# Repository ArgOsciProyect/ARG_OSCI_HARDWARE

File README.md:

# ARG_OSCI Hardware Implementation Guide

**ARG_OSCI** is an open-source portable oscilloscope platform. This document details the technical implementation of the hardware, focusing on design decisions, construction, and improvement opportunities. It is intended for engineers and advanced users interested in building or modifying the device.

---

## Table of Contents
- [Introduction](#introduction)
- [Design Overview](#design-overview)
- [Implementation Details](#implementation-details)
  - [1. Input Network](#1-input-network)
  - [2. Attenuation Networks](#2-attenuation-networks)
    - [2.1 A/B Attenuation Network](#ab-attenuation-network)
    - [2.2 1/2/3/4 Attenuation Network](#1234-attenuation-network)
    - [2.3 Attenuation Stage Details](#attenuation-stage-details)
  - [3. Amplification Stage](#3-amplification-stage)
  - [4. Signal Filtering](#4-signal-filtering)
  - [5. External ADC Circuit](#5-external-adc-circuit)
  - [6. Transient Comparator Circuit](#6-transient-comparator-circuit)
  - [7. Calibration Square Wave Generator](#7-calibration-square-wave-generator)
  - [8. Connection Status LED Circuit](#8-connection-status-led-circuit)
  - [9. Power Supply](#9-power-supply)
  - [10. ESP32 Connectivity and Decoupling](#10-esp32-connectivity-and-decoupling)
- [Design Files and Resources](#design-files-and-resources)
- [Construction and Improvement Notes](#construction-and-improvement-notes)
  - [1. Assembly and Component Selection](#assembly-and-component-selection)
  - [2. Protection and Safety](#protection-and-safety)
  - [3. Optional Simplifications](#optional-simplifications)
  - [4. Design and Layout](#design-and-layout)
  - [5. PCB Design](#pcb-design)
  - [6. 3D Case Design](#3d-case-design)
- [Pending Tasks and Recommendations](#pending-tasks-and-recommendations)
  - [1. Technical Improvements](#technical-improvements)
  - [2. Documentation and Usability](#documentation-and-usability)
  - [3. Future Development](#future-development)
- [License](#license)
- [Acknowledgements](#acknowledgements)

---

## Introduction

This document describes how to implement the ARG_OSCI hardware, including the rationale behind each design block, construction notes, and suggestions for further development. For usage instructions, refer to the user manual.

## Design Overview

The hardware is divided into several functional blocks:

- Input Network
- Attenuation Networks
- Attenuation Stage Details
- Amplification Stage
- Signal Filtering
- External ADC Circuit
- Transient Comparator Circuit
- Calibration Square Wave Generator
- Connection Status LED Circuit
- Power Supply
- ESP32 Connectivity and Decoupling

---

## Implementation Details

### 1. Input Network

The input network provides both AC and DC coupling paths. The AC coupling path includes a series capacitor (150 nF), while the DC path is direct. The 150 nF capacitor must be rated for at least 500V to safely block DC voltages up to the device's maximum scale (±400V). The capacitor value was selected to achieve a cutoff frequency below 1 Hz, considering that the input impedance is always greater than 1MΩ (typically 1070 MΩ to 1500 MΩ, depending on the attenuation setting). This configuration forms a high-pass filter and ensures accurate measurement of AC signals above 1Hz, with a settling time of approximately 1 second after switching to AC coupling.

<!--**Expansion note:** You may add a graph of the high-pass filter response.-->

### 2. Attenuation Networks
#### 2.1. A/B Attenuation Network
Provides coarse attenuation (e.g., ×40) using resistor dividers and mechanical switches (2P2T selector switch).

#### 2.2. 1/2/3/4 Attenuation Network
Provides fine attenuation (e.g., ×2.4), yielding eight selectable voltage ranges in combination with the A/B network. This stage also uses mechanical switches (2P4T selector switch) and resistor divider networks for attenuation.

#### 2.3. Attenuation Stage Details

The decision to use resistive divider networks in the attenuation stage was made after a thorough analysis of various possible configurations. Different approaches were evaluated based on criteria such as ease of compensation, the number of switches required for implementation, the impedance presented to the amplifier, and other relevant aspects. The chosen solution represents a balance between precision, simplicity, and robustness for the application.

The attenuation stage is designed to maintain an input impedance greater than 1 MΩ. To compensate for the effects of parasitic capacitances —particularly those introduced by the amplifier— capacitors are included in the attenuation network. The total input capacitance of the device is kept below 20pF. Components are selected with 5% tolerance (1% for higher precision if desired), resistors are rated at 1/4 W, and capacitors are rated for at least 25 V, except for the series capacitor in stage B, which must withstand up to 500 V to safely attenuate signals up to 400V when required.

A trimmer capacitor is placed at the amplifier input to allow fine adjustment and compensate for variations in the amplifier’s input capacitance and other component tolerances. The trimmer is adjustable up to 20pF, with a minimum value of approximately 4.2pF, ensuring a flat frequency response across the device’s bandwidth. The most sensitive stage to these variations is A2, as it has the smallest capacitance in parallel with the amplifier, making it more susceptible to frequency response deviations.

### 3. Amplification Stage

The amplification stage uses the TL082 operational amplifier, chosen for its suitable bandwidth, slew rate, operating ranges, low associated errors, low cost, and ease of sourcing. Two feedback configurations are implemented: the inverting configuration is used to set the signal offset (centering it within the ADC input range using the –5V rail), while the non-inverting configuration amplifies the measured signal to maximize the ADCs' dynamic range.

To minimize errors due to input bias currents, high-value resistors are used in the feedback network. This necessitated the inclusion of a capacitive compensation network (without the need for a trimmer in this case).

<!--**Expansion note:** Discuss op-amp selection criteria, possible improvements, and test results.-->

#### Design Considerations and Potential Improvements
- **Resistor Value Optimization:** It is being considered to reduce the values of the feedback resistors, as the error from bias currents is relatively low. Lowering these values could allow the removal of the compensation network, though a capacitor should still be retained to filter noise from the –5V supply. This change would increase the device's power consumption and should be evaluated accordingly.
- **Negative Voltage Limiter:** It is recommended to add a negative voltage limiter at the amplifier output. While the amplifier typically saturates at positive voltages (not damaging the ADCs), under certain conditions it may output voltages below 0V, which could potentially harm the ADCs.

### 4. Signal Filtering

A conventional first-order RC low-pass filter is used for signal filtering. The filters are designed based on the input capacitance of the ADCs used in each case. Two separate filter networks are implemented, allowing the user to select which ADC to use. For each network, the cutoff frequency is set to the maximum frequency that the device can accurately measure with the selected ADC.

#### Design Considerations and Potential Improvements
- **Filter Effectiveness Review:** It has been observed that at higher frequencies, aliasing phenomena may occur, distorting the measured signal and its frequency spectrum. A review of the filter effectiveness is recommended, and higher-order filters may be considered to improve performance and reduce aliasing effects.

### 5. External ADC Circuit

The external ADC (ADS7884) circuit is designed following the manufacturer's recommendations. For SPI communication with the ESP32, the layout ensures physical proximity between the ADS7884 and the relevant ESP32 pins, with all SPI traces kept as short and equal in length as possible. These measures are critical to maintain signal integrity at the 40 MHz communication frequency.

The ADS7884 is powered by the 3.3 V supply provided by the ESP32's onboard regulator, which also serves as the ADC's voltage reference. The stability of this voltage is crucial for measurement accuracy. To stabilize the supply, an RC network is implemented, consisting of the manufacturer-recommended capacitors and a 100 Ω resistor (subject to further review), in line with the recommended power supply impedance.

#### Design Considerations and Potential Improvements
- **Dedicated Voltage Regulator:** It is recommended to consider adding a dedicated voltage regulator for the ADC to ensure a stable reference voltage, independent of noise from the ESP32 supply.
- **Power Supply Filtering Review:** The value of the series resistor and the overall RC network should be reviewed and optimized to further improve voltage stability and measurement quality.
- **EMI/Environmental Noise Shielding:** The ADC has shown sensitivity to environmental interference and noise. It is recommended to implement shielding methods on the PCB or enclosure to reduce these effects and improve measurement reliability.

### 6. Transient Comparator Circuit

The transient comparator circuit enables the detection and reading of aperiodic (transient) signals. It consists of three main parts, each with a specific function:

#### RC Filter
The RC filter stabilizes a PWM signal generated by the ESP32. This PWM signal is set to have an average voltage equal to the trigger level selected in the application for signal visualization. The resulting DC voltage serves as the reference level for the comparator.

#### Comparator (TL082)
The remaining amplifier in the TL082 IC is configured as a comparator. It compares the measured signal to the reference voltage from the RC filter. When the input signal exceeds the trigger threshold, the comparator switches its output state. This transition is recognized as a transient event, which is then communicated to the application for display.

#### Digital Signal Adapter
The digital adapter converts the output of the comparator to voltage levels that are safe and readable by the ESP32: 3.3 V (minimum 2.475 V) for logic high and 0 V (maximum 0.825 V) for logic low. This is achieved using a BAT54 (or BAT85) diode in combination with a resistive divider, which limits current and ensures the output is pulled close to 0 V when the comparator switches to its negative output.

<!--**Expansion note:** Add timing diagrams or oscilloscope captures of transient detection events.-->

### 7. Calibration Square Wave Generator

The calibration circuit operates using a 1 kHz square wave signal provided by the ESP32, with levels ranging from 0 V to 3.3 V. This signal is attenuated to approximately 30% of its original amplitude using a resistive divider (15 kΩ and 6.8 kΩ), resulting in a safe level for the A2 stage, which is particularly sensitive to parasitic capacitance. The attenuated signal is used specifically to fine-tune the trimmer capacitor in the A2 stage. The resistor values are selected to minimize current draw and reduce loading on the ESP32 output.

### 8. Connection Status LED Circuit

The purpose of this LED is to indicate when the ESP32 board is ready to accept WiFi connections and begin operation. While the LED is off, the device is generating the access point. When the LED turns on, it signals that the user can connect to the device.

A 5 mm LED is used to increase visibility. A 270 Ω resistor is placed in series, but this value can be adjusted if needed—for example, using a lower resistance to increase brightness. The LED size and resistor value can be modified according to specific design preferences.

### 9. Power Supply
#### 9.1. +5V Supply
- The +5V supply is sourced from the ESP32's 5V pin, which itself is powered via the USB port.
- A diode-capacitor circuit is used between the USB input and the 5V rail. The presence of the diode causes a slight voltage drop below 5V. While this does not affect the operation of the operational amplifiers, it does slightly shift the voltage levels in the comparator circuit and significantly impacts the generation of the –5V rail via the LM2776.

#### 9.2. –5V Supply
- The –5V rail is generated using the LM2776 charge pump IC, implemented according to the manufacturer's recommendations.
- Stabilization and voltage generation capacitors are placed as close as possible to the LM2776 to ensure proper operation and minimize noise.
- Since the LM2776 inverts and slightly alters the positive supply voltage, software and firmware corrections are applied to compensate for any offset shifts that could affect ADC readings.
- There is a known issue with the LM2776 operation that requires further review to ensure reliable negative voltage generation.

#### 9.3. External Power Option
- The PCB provides access to power supply pins, allowing the circuit to be powered externally. This enables bypassing the micro USB and ESP32 for power delivery, and allows for a higher-quality negative voltage supply if needed.

### 10. ESP32 Connectivity and Decoupling
#### 10.1. Future Improvements
- **Direct Microcontroller Integration:** There are plans to redesign the hardware to use only the ESP32 microcontroller chip, eliminating the full devkit. This would:
  - Reduce the overall PCB size
  - Simplify flashing and programming
  - Improve signal routing and reduce parasitic effects
  - Allow for more flexible and compact enclosure designs
  - Potentially reduce cost and improve reliability

---

## Design Files and Resources
- **Schematics**: Complete circuit diagrams for all hardware blocks. Located in the ['Schematics'](Schematics/) folder.
- **PCB Layout**: Proposed PCB design with Gerber files for manufacturing. Located in the ['PCB'](PCB/) folder.
- **BOM**: Bill of Materials with recommended part numbers and tolerances. Available in the ['BOM'](BOM/) folder.
- **3D Enclosure**: Printable STL files for the device enclosure. Available in the ['Case3D'](Case3D/) folder.
- **LTspice Simulations**: Circuit simulation files for analysis and design validation. Recommended folder name: ['LTspice_Simulations'](LTspice_Simulations/).

> **Additional files:**
- Technical documentation and manuals in the ['Doc'](Doc/) folder.
- Images and diagrams in the ['Images'](Images/) folder.

---

## Construction and Improvement Notes

### 1. Assembly and Component Selection
- For best measurement accuracy, use 1% tolerance components in the following order of priority:
  1. Amplification circuit (affects all scales and frequencies)
  2. A/B attenuation circuit (affects upper half of scales, 40x attenuation)
  3. Series capacitor in the 1/2/3/4 attenuation circuit (affects all scales at high frequency)
  4. 1/2/3/4 attenuation circuit (affects all scales)
  5. Input filters to the ADCs
  6. Remaining components
- Both the internal ESP32 ADC and the external ADC present nonlinearities, though the external ADC is more accurate.
- Pay special attention to the correct wiring of the attenuation scales and selector logic during assembly. Errors here can damage multiple components.

### 2. Protection and Safety
- It is strongly recommended to add fuse-varistor protection circuits to safeguard the integrity of the attenuation stages:
  - 12.5 V varistor in stage A
  - 500 V varistor in stage B
  - 5 V varistor in stage 1 (direct path to the op-amp)

Note: The current PCB does not include footprints for these components.

### 3. Optional Simplifications
- The following stages can be omitted to reduce PCB size, simplify construction, or save on materials:
  - B attenuation stage (if high-voltage operation is not required)
  - AC/DC selection stage
  - Single-shot mode stage
  - ADC input filter for any unused ADC
- If the LM2776 IC is unavailable, substitute with a similar IC (ensure correct pinout) or provide a negative voltage rail externally.

### 4. Design and Layout
- PCB layout can be further optimized for EMC and signal integrity.
- The enclosure design may be adapted or improved for robustness.
- More compact PCB designs are planned, including protection features and direct microcontroller integration (without the devkit).

### 5. PCB Design
The PCB was designed following standard practices, prioritizing functional block separation and signal integrity as described in previous sections. No special layout considerations beyond those already mentioned were required.

### 6. 3D Case Design
The 3D case was designed to fit the PCB and provide basic protection. No special design constraints or requirements were considered beyond ensuring proper fit.

> **Note:** If electromagnetic shielding is desired to reduce interference, keep in mind that the device connects via WiFi. Any shielding solution should be implemented with care to avoid degrading wireless communication performance.

---

## Pending Tasks and Recommendations

### 1. Technical Improvements
- Complete a detailed error analysis and document the results for all acquisition paths.
- Review and improve the negative power supply design, including alternatives to the LM2776.
- Consider implementing higher-order input filters to improve signal fidelity and reduce aliasing.
- Evaluate and document the effectiveness of protection circuits and their impact on measurement reliability.

### 2. Documentation and Usability
- Provide step-by-step assembly instructions and detailed test procedures.
- Add troubleshooting and known issues sections to assist users during assembly and operation.

### 3. Future Development
- Develop and release more compact PCB designs with integrated protections and without the devkit.
- Explore the possibility of omitting or modularizing optional stages for different use cases.

---

## License

This hardware project is licensed under the [CERN-OHL-W v2](https://gitlab.com/ohwr/project/cernohl/-/wikis/home).

---

## Acknowledgements

This project is part of the **ARG_OSCI** oscilloscope visualization tool suite. For firmware and software, visit the [ARG_OSCI_FIRMWARE](https://github.com/ArgOsciProyect/ARG_OSCI_FIRMWARE) and [ARG_OSCI_APP](https://github.com/ArgOsciProyect/ARG_OSCI_APP) repositories.

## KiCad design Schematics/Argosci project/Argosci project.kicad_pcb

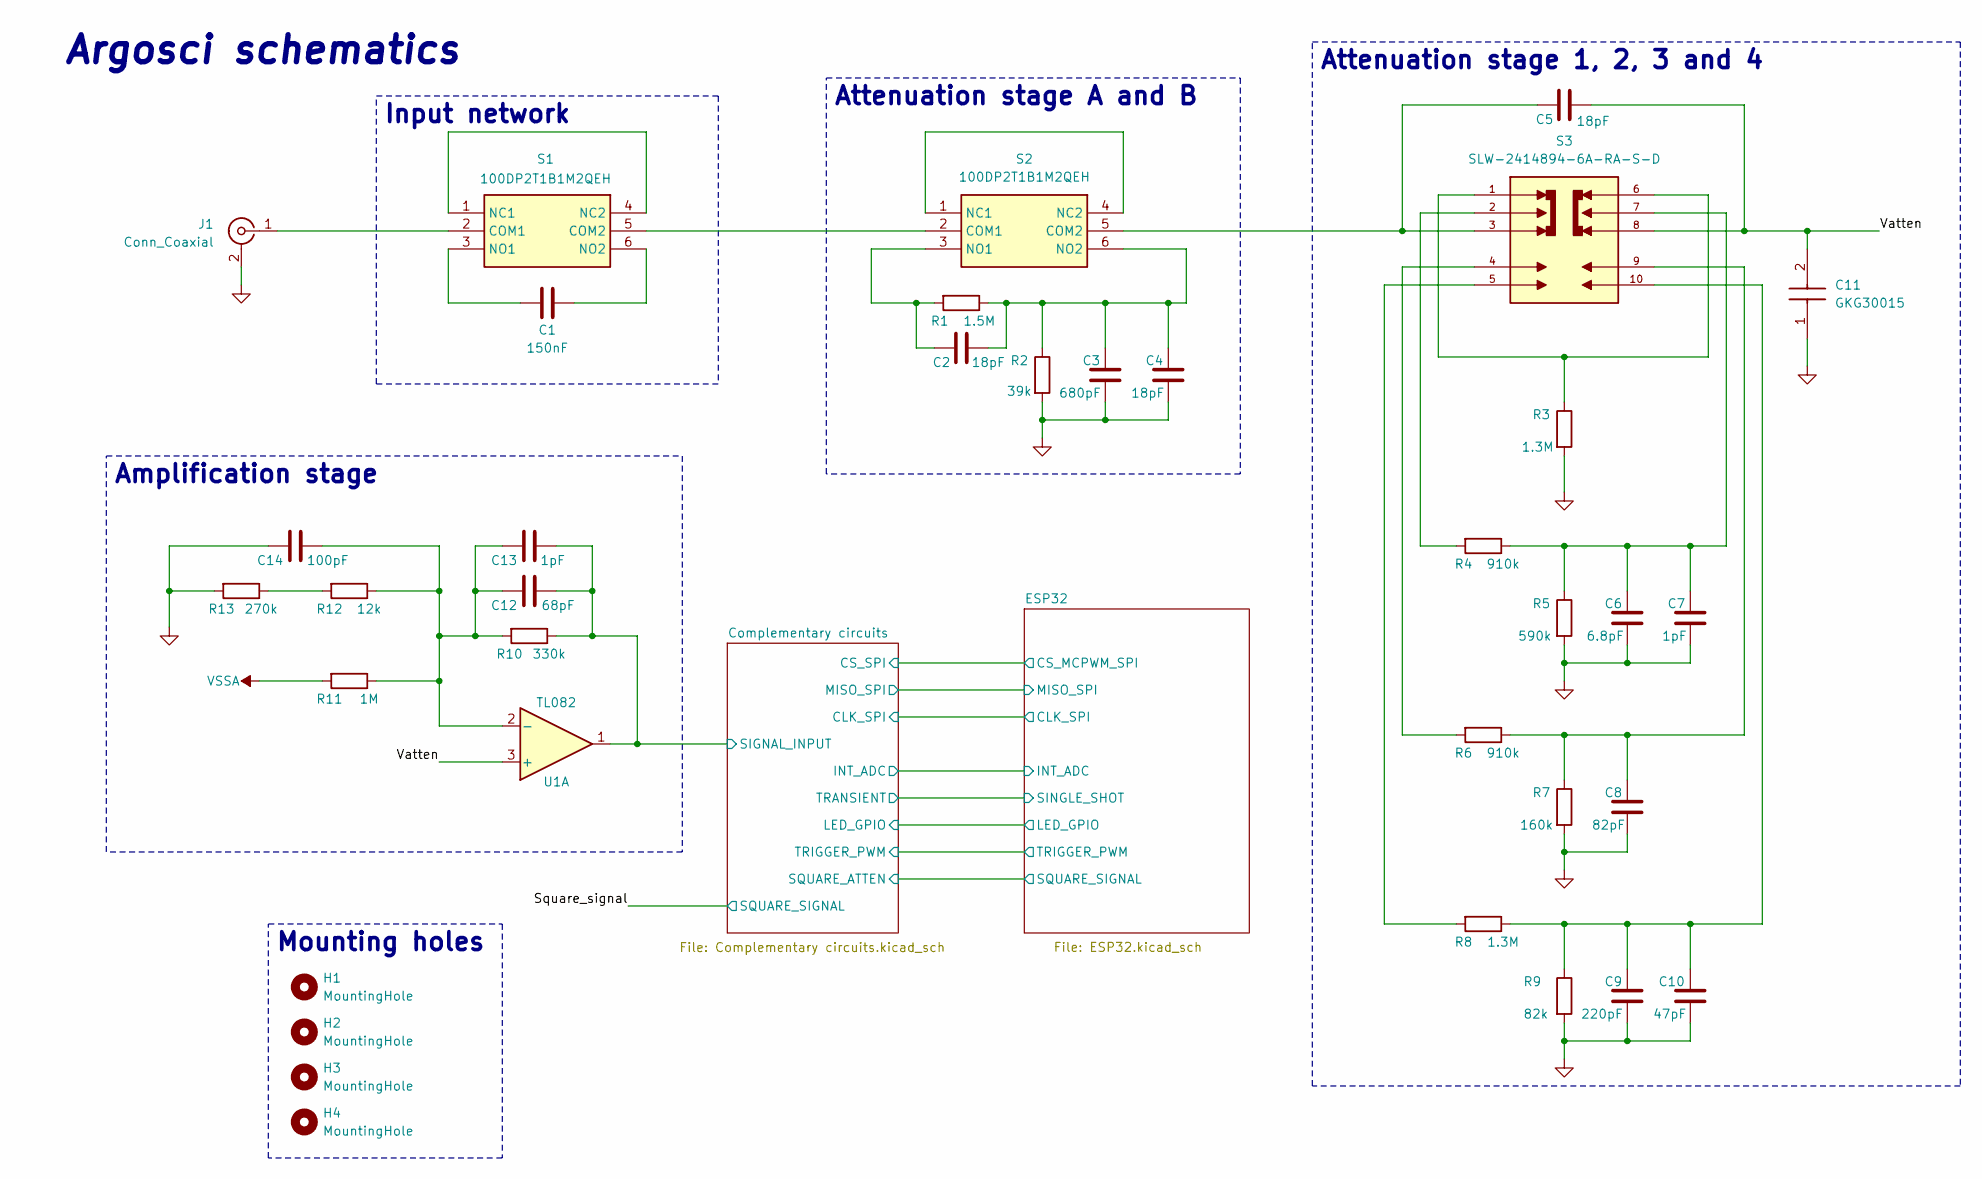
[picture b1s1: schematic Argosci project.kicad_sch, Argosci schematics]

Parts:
C1: 150nF; C_1206_3216Metric
C2, C4, C5: 18pF; C_1206_3216Metric
C3: 680pF; C_1206_3216Metric
C6: 6.8pF; C_1206_3216Metric
C7, C13: 1pF; C_1206_3216Metric
C8: 82pF; C_1206_3216Metric
C9: 220pF; C_1206_3216Metric
C10: 47pF; C_1206_3216Metric
C11: GKG30015; Mouser Part Number 659-GKG30015
C12: 68pF; C_1206_3216Metric
C14: 100pF; C_1206_3216Metric
H1, H2, H3, H4: MountingHole; MountingHole_3mm
J1: Conn_Coaxial; BNC_Amphenol_B6252HB-NPP3G-50_Horizontal
R1: 1.5M; R_1206_3216Metric
R2: 39k; R_1206_3216Metric
R3, R8: 1.3M; R_1206_3216Metric
R4, R6: 910k; R_1206_3216Metric
R5: 590k; R_1206_3216Metric
R7: 160k; R_1206_3216Metric
R9: 82k; R_1206_3216Metric
R10: 330k; R_1206_3216Metric
R11: 1M; R_1206_3216Metric
R12: 12k; R_1206_3216Metric
R13: 270k; R_1206_3216Metric
S1, S2: 100DP2T1B1M2QEH; Mouser Part Number 612-100DP2T1B1M2QEH
S3: SLW-2414894-6A-RA-S-D; SW_SLW-2414894-6A-RA-S-D; PARTREV 1.01
U1: TL082; DIP-8_W7.62mm

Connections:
/Complementary circuits/SIGNAL_INPUT: C12.2, C13.2, R10.1, U1.1; also elsewhere on the board
/Vatten: C5.2, C11.2, S3.8, U1.3 (+)
GND: C3.2, C4.2, C6.2, C7.2, C8.2, C9.2, C10.2, C11.1, C14.1, J1.2 (Ext), R2.2, R3.2, R5.2, R7.2, R9.2, R13.2; also elsewhere on the board
unnamed: C6.1, C7.1, R4.1, R5.1, S3.7
unnamed: C8.1, R6.1, R7.1, S3.9
unnamed: C9.1, C10.1, R8.1, R9.1, S3.10
unnamed: J1.1 (In), S1.2 (COM1)
unnamed: R3.1, S3.1, S3.6
unnamed: R4.2, S3.2
unnamed: R6.2, S3.4
unnamed: R8.2, S3.5
unnamed: R12.2, R13.1
unnamed: S1.5 (COM2), S2.2 (COM1)
unnamed: S1.1 (NC1), S1.4 (NC2)
unnamed: C1.1, S1.3 (NO1)
unnamed: C1.2, S1.6 (NO2)
unnamed: C5.1, S2.5 (COM2), S3.3
unnamed: S2.1 (NC1), S2.4 (NC2)
unnamed: C2.1, R1.2, S2.3 (NO1)
unnamed: C2.2, C3.1, C4.1, R1.1, R2.1, S2.6 (NO2)
unnamed: C12.1, C13.1, C14.2, R10.2, R11.1, R12.1, U1.2 (-)
VSSA: R11.2; also elsewhere on the board

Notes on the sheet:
Argosci schematics
Input network
Mounting holes
Amplification stage
Attenuation stage 1, 2, 3 and 4
Attenuation stage A and B

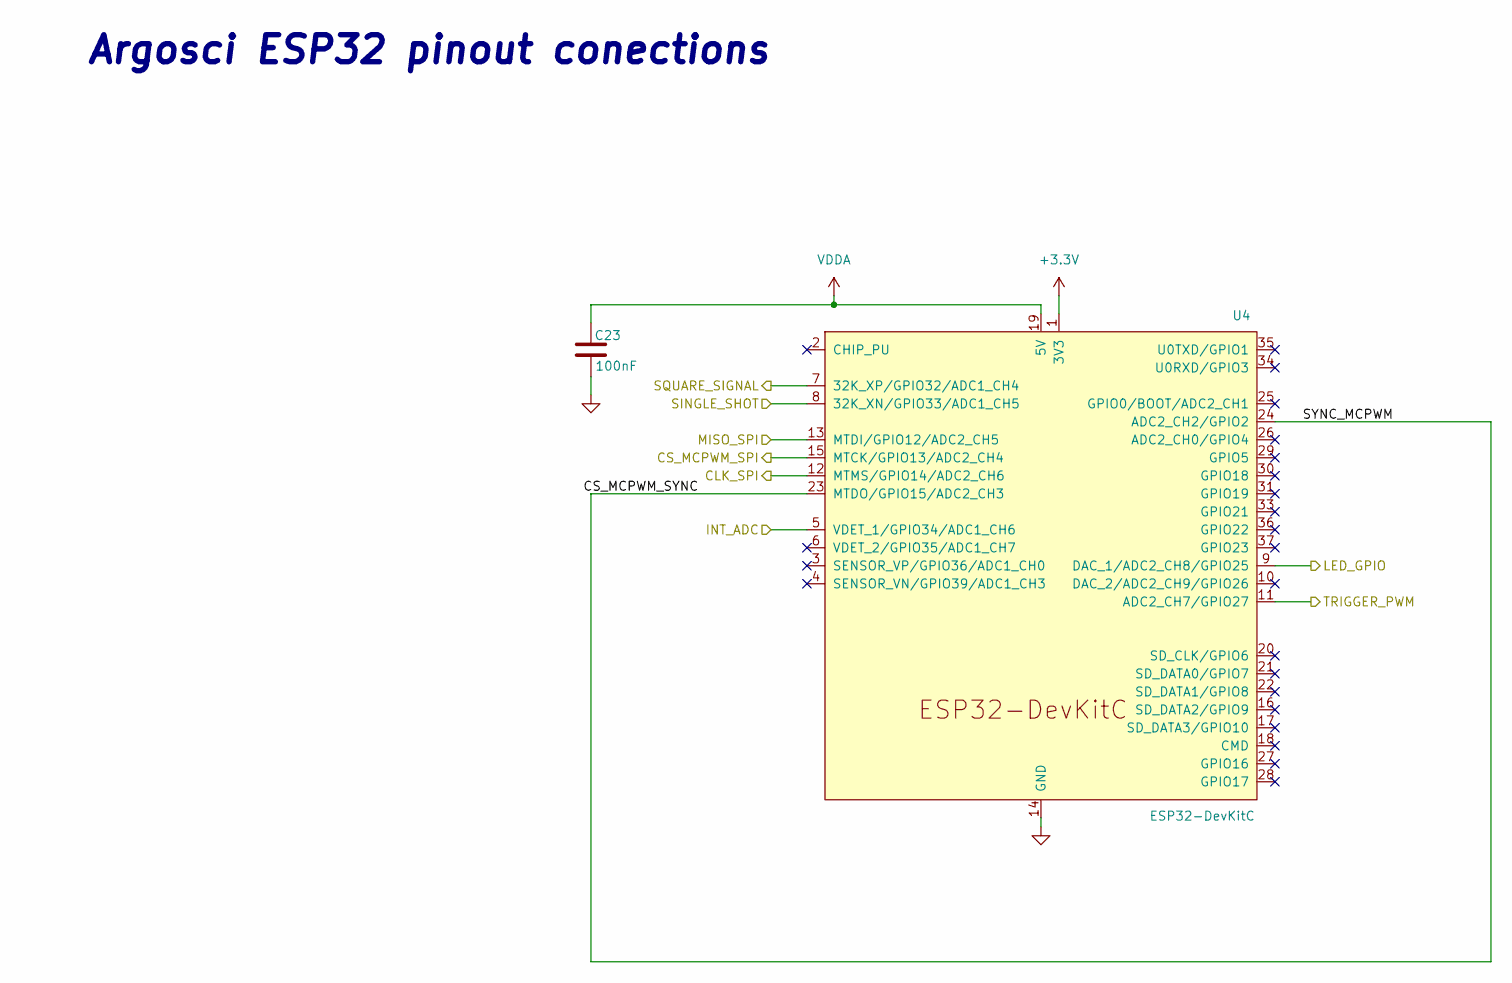
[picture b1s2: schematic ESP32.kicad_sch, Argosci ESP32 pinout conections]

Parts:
C23: 100nF; C_1206_3216Metric
U4: ESP32-DevKitC

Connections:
+3.3V: U4.1 (3V3); also elsewhere on the board
/Complementary circuits/CLK_SPI: U4.12 (MTMS/GPIO14/ADC2_CH6); also elsewhere on the board
/Complementary circuits/CS_SPI: U4.15 (MTCK/GPIO13/ADC2_CH4); also elsewhere on the board
/Complementary circuits/INT_ADC: U4.5 (VDET_1/GPIO34/ADC1_CH6); also elsewhere on the board
/Complementary circuits/LED_GPIO: U4.9 (DAC_1/ADC2_CH8/GPIO25); also elsewhere on the board
/Complementary circuits/MISO_SPI: U4.13 (MTDI/GPIO12/ADC2_CH5); also elsewhere on the board
/Complementary circuits/SQUARE_ATTEN: U4.7 (32K_XP/GPIO32/ADC1_CH4); also elsewhere on the board
/Complementary circuits/TRANSIENT: U4.8 (32K_XN/GPIO33/ADC1_CH5); also elsewhere on the board
/Complementary circuits/TRIGGER_PWM: U4.11 (ADC2_CH7/GPIO27); also elsewhere on the board
/ESP32/CS_MCPWM_SYNC: U4.23 (MTDO/GPIO15/ADC2_CH3), U4.24 (ADC2_CH2/GPIO2)
GND: C23.2, U4.14 (GND), U4.32 (GND), U4.38 (GND); also elsewhere on the board
VDDA: C23.1, U4.19 (5V); also elsewhere on the board

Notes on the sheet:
Argosci ESP32 pinout conections

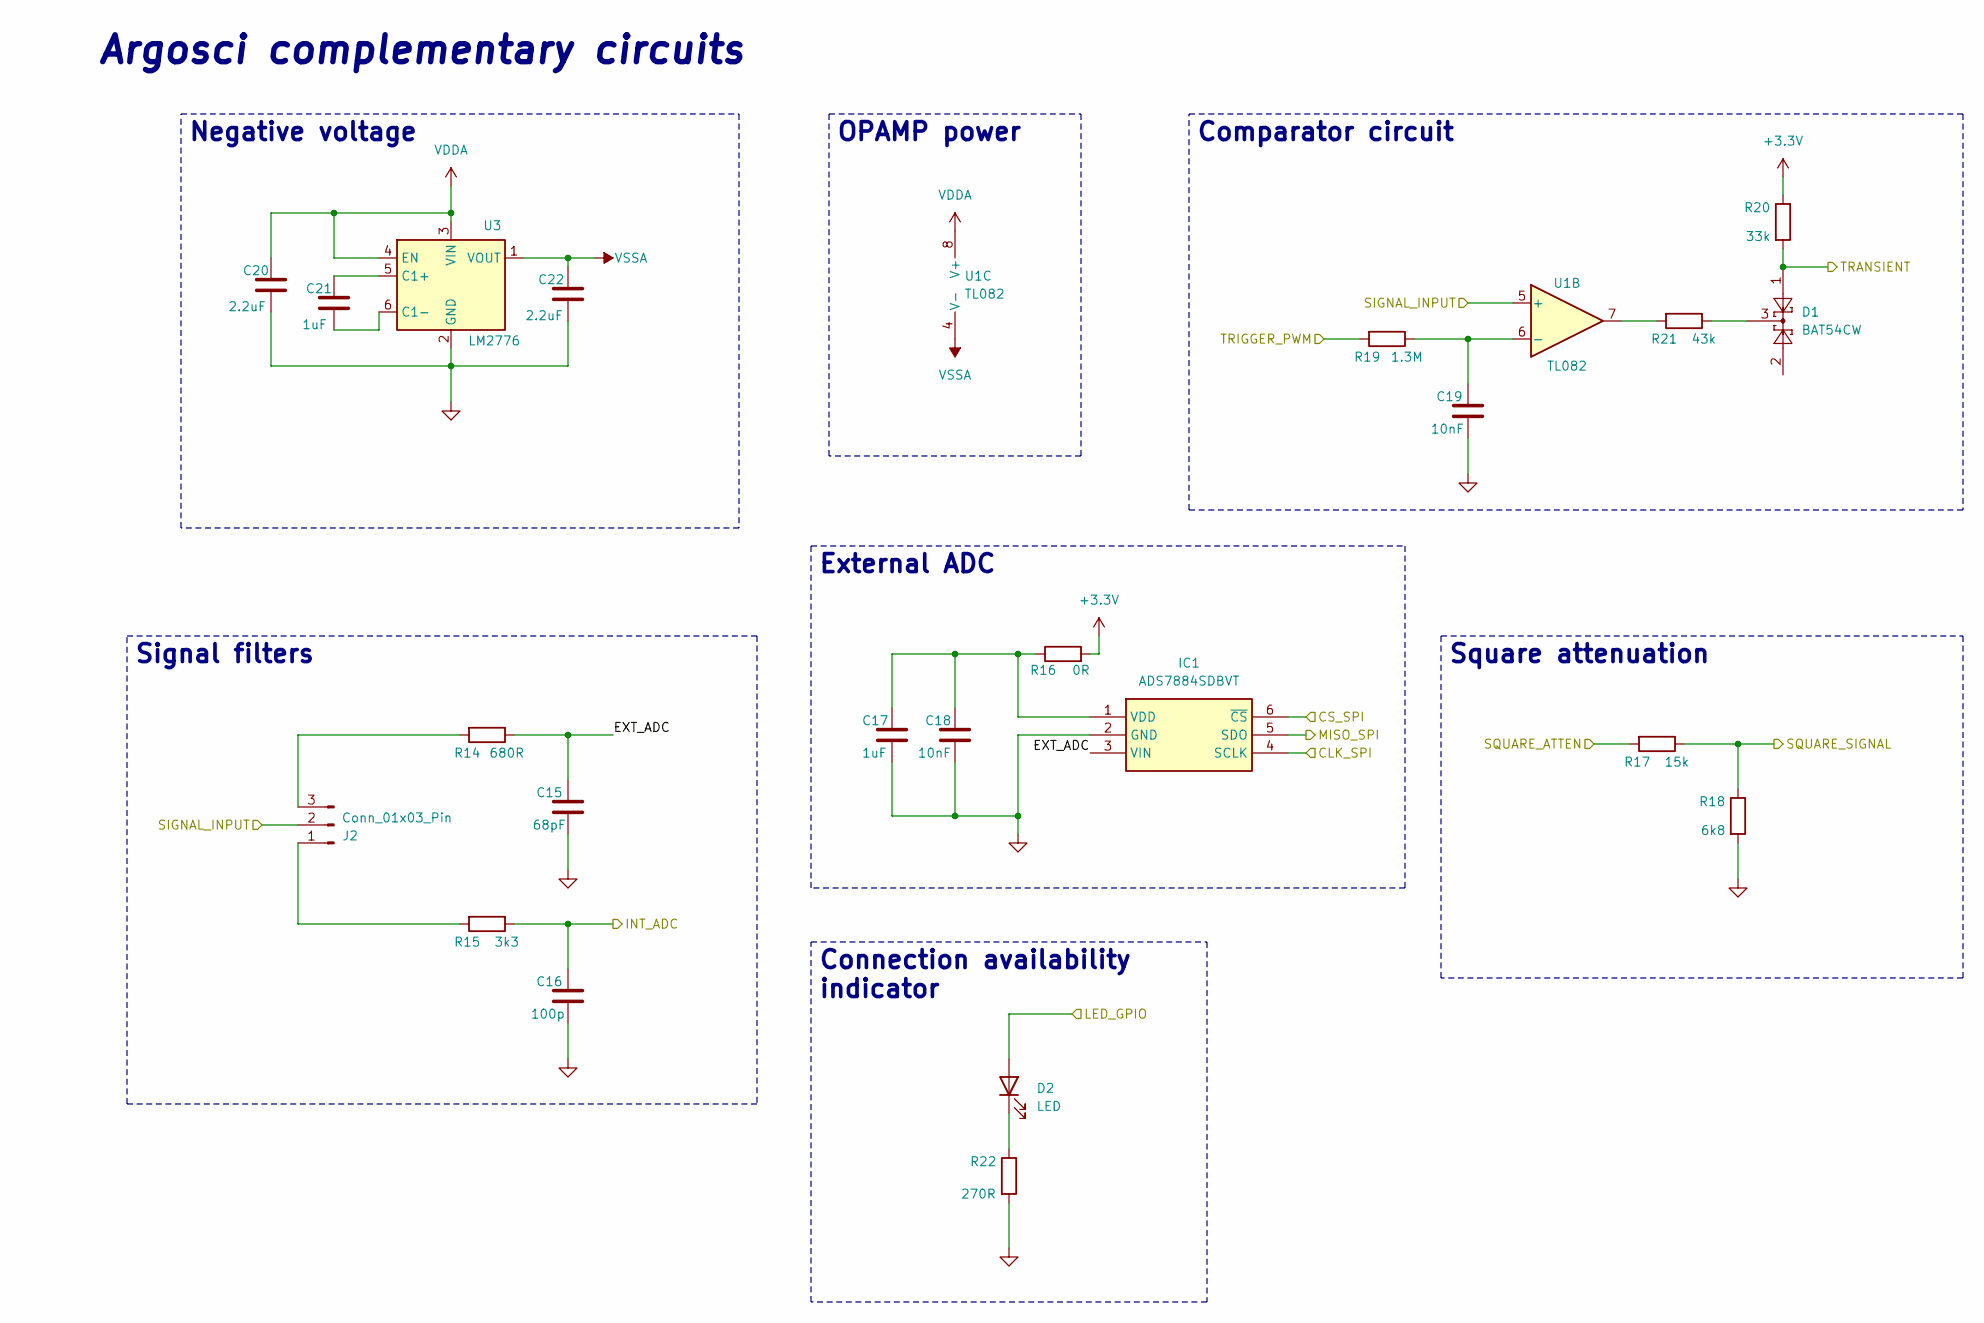
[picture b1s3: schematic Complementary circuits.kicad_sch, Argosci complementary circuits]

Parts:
C15: 68pF; C_1206_3216Metric
C16: 100p; C_1206_3216Metric
C17, C21: 1uF; C_1206_3216Metric
C18, C19: 10nF; C_1206_3216Metric
C20, C22: 2.2uF; C_1206_3216Metric
D1: BAT54CW; SOT-323_SC-70
D2: LED; LED_D5.0mm
IC1: ADS7884SDBVT; SOT95P280X145-6N; Mouser Part Number 595-ADS7884SDBVT
J2: Conn_01x03_Pin; PinHeader_1x03_P2.54mm_Vertical
R14: 680R; R_1206_3216Metric
R15: 3k3; R_1206_3216Metric
R16: 0R; R_1206_3216Metric
R17: 15k; R_1206_3216Metric
R18: 6k8; R_1206_3216Metric
R19: 1.3M; R_1206_3216Metric
R20: 33k; R_1206_3216Metric
R21: 43k; R_1206_3216Metric
R22: 270R; R_1206_3216Metric
U1: TL082; DIP-8_W7.62mm
U3: LM2776; SOT-23-6

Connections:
+3.3V: R16.2, R20.1; also elsewhere on the board
/Complementary circuits/CLK_SPI: IC1.4 (SCLK); also elsewhere on the board
/Complementary circuits/CS_SPI: IC1.6 (~CS); also elsewhere on the board
/Complementary circuits/EXT_ADC: C15.1, IC1.3 (VIN), R14.1
/Complementary circuits/INT_ADC: C16.1, R15.1; also elsewhere on the board
/Complementary circuits/LED_GPIO: D2.2 (A); also elsewhere on the board
/Complementary circuits/MISO_SPI: IC1.5 (SDO); also elsewhere on the board
/Complementary circuits/SIGNAL_INPUT: J2.2, U1.5 (+); also elsewhere on the board
/Complementary circuits/SQUARE_ATTEN: R17.2; also elsewhere on the board
/Complementary circuits/TRANSIENT: D1.1, R20.2; also elsewhere on the board
/Complementary circuits/TRIGGER_PWM: R19.2; also elsewhere on the board
/Square_signal: R17.1, R18.1
GND: C15.2, C16.2, C17.2, C18.2, C19.2, C20.2, C22.2, IC1.2 (GND), R18.2, R22.2, U3.2 (GND); also elsewhere on the board
unnamed: D1.3, R21.1
unnamed: D2.1 (K), R22.1
unnamed: C17.1, C18.1, IC1.1 (VDD), R16.1
unnamed: J2.1, R15.2
unnamed: J2.3, R14.2
unnamed: R21.2, U1.7
unnamed: C19.1, R19.1, U1.6 (-)
unnamed: C21.1, U3.5 (C1+)
unnamed: C21.2, U3.6 (C1-)
VDDA: C20.1, U1.8 (V+), U3.3 (VIN), U3.4 (EN); also elsewhere on the board
VSSA: C22.1, U1.4 (V-), U3.1 (VOUT); also elsewhere on the board

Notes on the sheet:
Argosci complementary circuits
Signal filters
Connection availability indicator
Square attenuation
External ADC
Negative voltage
OPAMP power
Comparator circuit

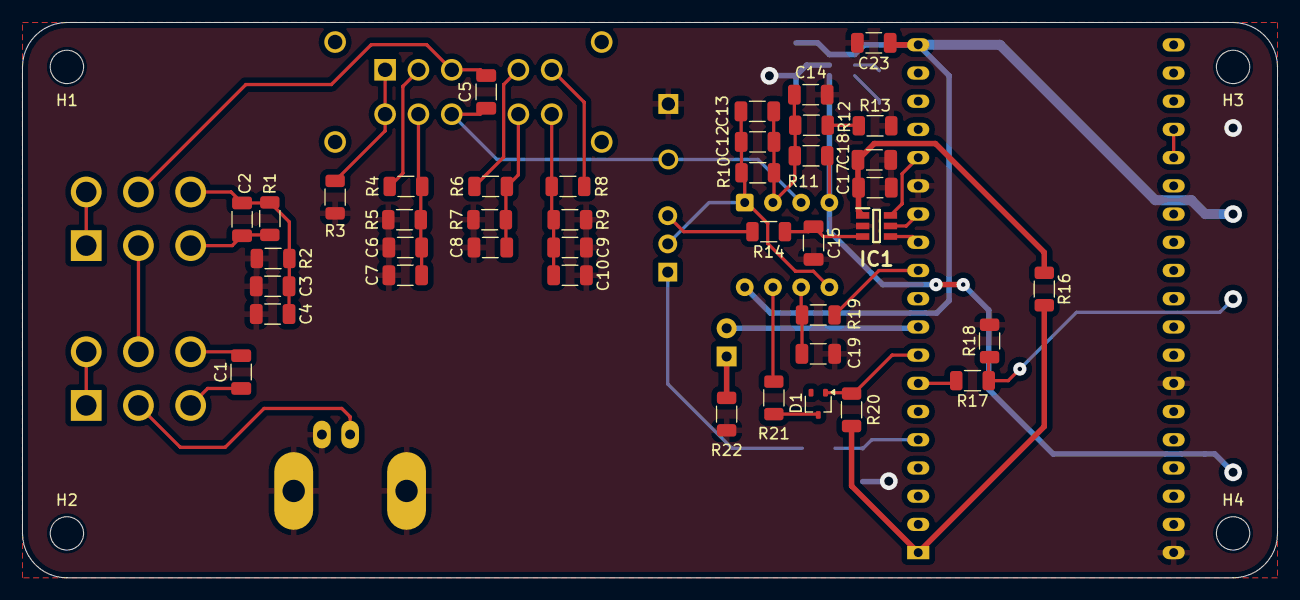
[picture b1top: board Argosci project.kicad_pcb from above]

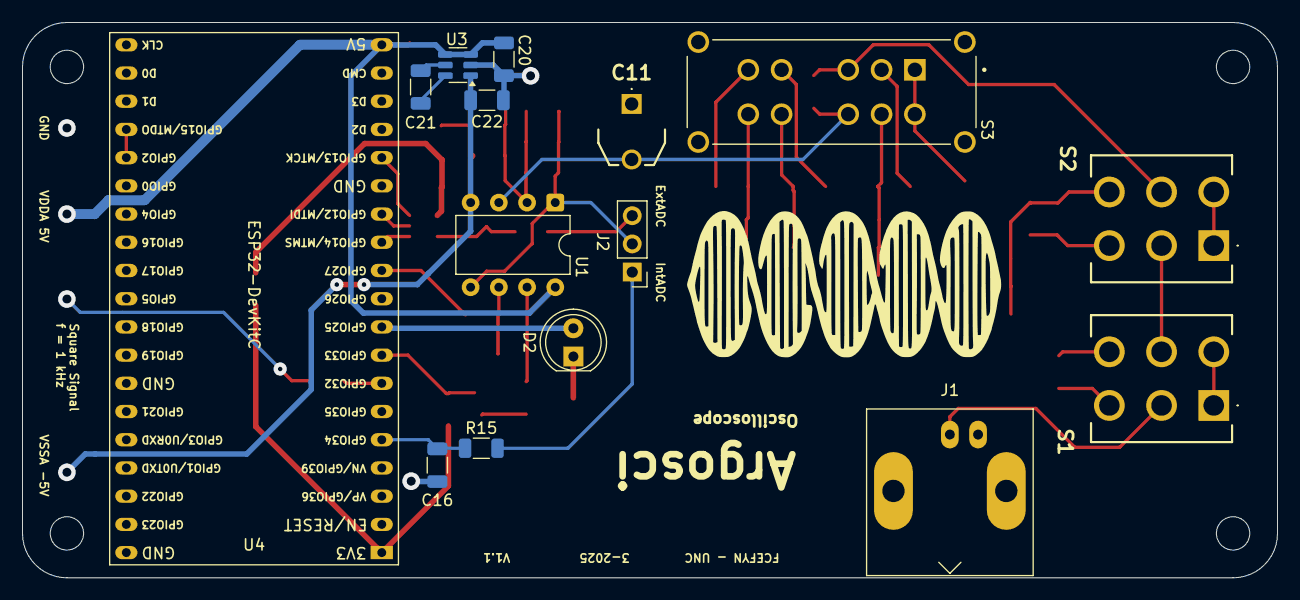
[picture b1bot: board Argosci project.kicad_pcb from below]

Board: 2 copper layers, 113.0 x 50.0 mm, 60 parts (15 on the bottom side), 44 nets.

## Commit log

2025-04-08 First update README.md
2025-04-14 Rename Argosci Through-hole prototype.jpg to ArgosciThrough-holeprototype.jpg
2025-04-14 Rename Bot Side - Argosci PCB.png to BotSide-ArgosciPCB.png
2025-04-14 Rename Bot Side - PCB layout.png to BotSide-PCBlayout.png
2025-04-14 Rename Front-Right Isometric - Argosci PCB and case.png to Front-RightIsometric-ArgosciPCBandcase.png
2025-04-14 Rename Front-Right Isometric - Argosci PCB.png.png to Front-RightIsometric-ArgosciPCB.png
2025-04-14 Rename Front-Right Isometric - Argosci divided case.png to Front-RightIsometric-Argoscidividedcase.png
2025-04-14 Rename Rear-Left Isometric - Argosci PCB and case.png to Rear-Left_Isometric-Argosci_PCB_and_case.png
2025-04-14 Rename ArgosciThrough-holeprototype.jpg to Argosci_Through-hole_prototype.jpg
2025-04-14 Rename BotSide-ArgosciPCB.png to Bot_Side-Argosci_PCB.png
2025-04-14 Rename BotSide-PCBlayout.png to Bot_Side-PCB_layout.png
2025-04-14 Rename Front-RightIsometric-ArgosciPCB.png to Front-Right_Isometric-Argosci_PCB.png
2025-04-14 Rename Front-RightIsometric-ArgosciPCBandcase.png to Front-Right_Isometric-Argosci_PCB_and_case.png
2025-04-14 Rename Front-RightIsometric-Argoscidividedcase.png to Front-Right_Isometric-Argosci_divided_case.png
2025-04-14 Rename Simplified frequency response of the input scales.jpg to Simplified_frequency_response_of_the_input_scales.jpg
2025-04-14 Rename Top Side - Argosci PCB and case.png to Top_Side-Argosci_PCB_and_case.png
2025-04-14 Rename Top Side - Argosci PCB.png to Top_Side-Argosci_PCB.png
2025-04-14 Rename Top Side - PCB layout.png to Top_Side-PCB_layout.png
2025-04-14 Create LICENSE
2025-04-22 README_modifications
2025-04-23 README_updates
2025-04-28 3D case improvements

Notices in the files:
README.md:
This hardware project is licensed under the [CERN-OHL-W v2](https://gitlab.com/ohwr/project/cernohl/-/wikis/home).
License: CERN-OHL-W
